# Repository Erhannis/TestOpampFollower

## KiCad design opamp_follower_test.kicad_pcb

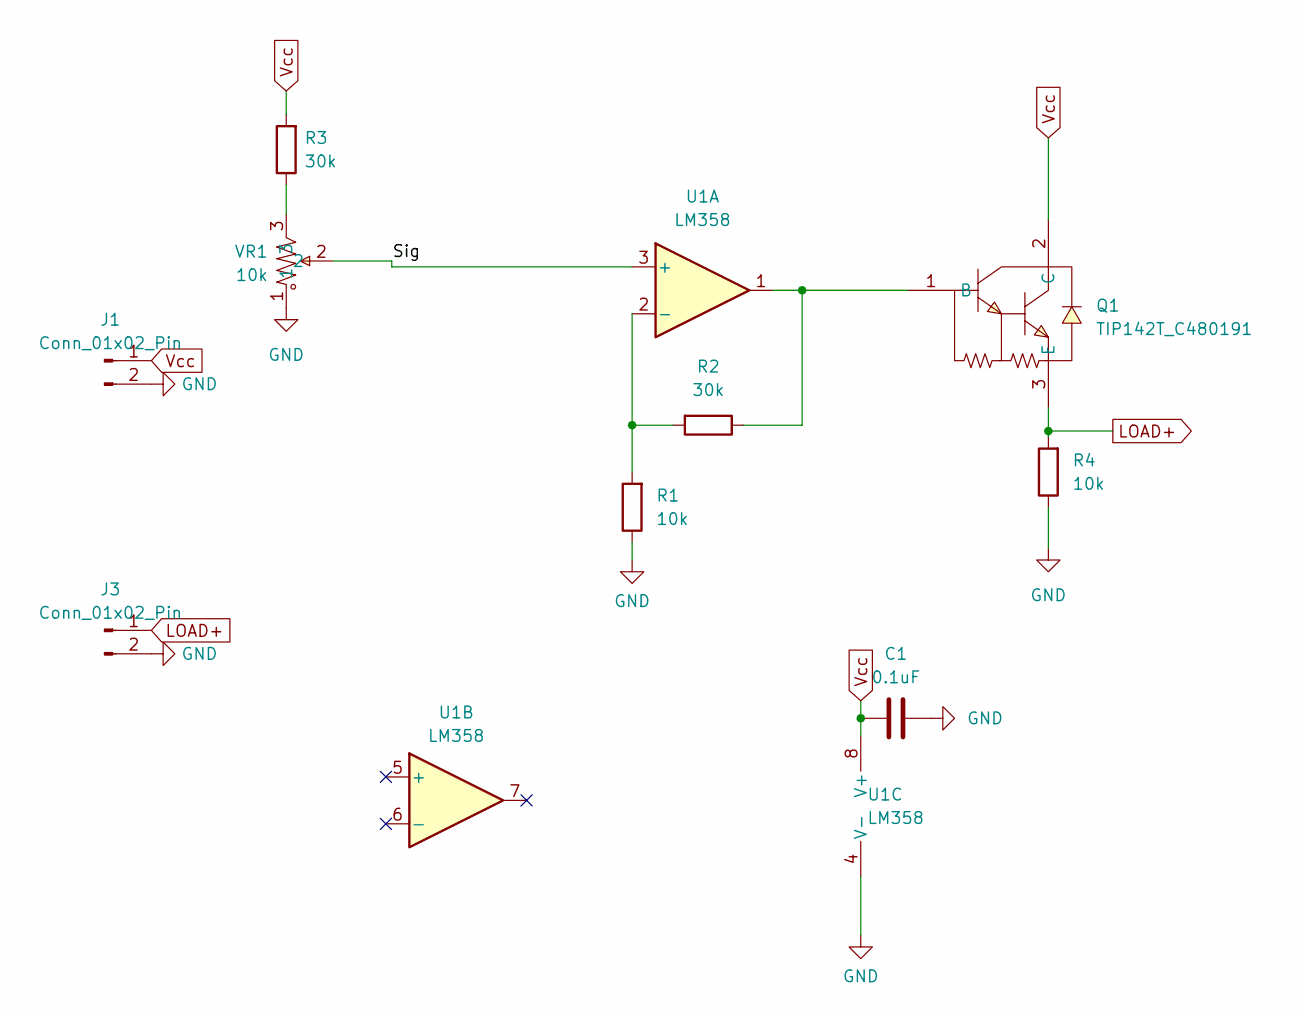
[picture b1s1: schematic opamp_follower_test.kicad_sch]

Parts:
C1: 0.1uF; C_0805_2012Metric
J1, J3: Conn_01x02_Pin; JST_NV_B02P-NV_1x02_P5.00mm_Vertical
Q1: TIP142T_C480191; TO-220-3_L10.1-W4.4-P2.54_IRF640NPBF; LCSC Part C480191
R1, R4: 10k; R_0805_2012Metric
R2, R3: 30k; R_0805_2012Metric
U1: LM358; DIP-8_W7.62mm
VR1: 10k; RES-ADJ-SMD_RM065-V1; LCSC Part C5205021

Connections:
/Sig: U1.3 (+), VR1.2
GND: C1.2, J1.2, J3.2, R1.1, R4.1, U1.4 (V-), VR1.1
LOAD+: J3.1, Q1.3 (E), R4.2
unnamed: Q1.1 (B), R2.1, U1.1
unnamed: R3.1, VR1.3
unnamed: R1.2, R2.2, U1.2 (-)
Vcc: C1.1, J1.1, Q1.2 (C), R3.2, U1.8 (V+)

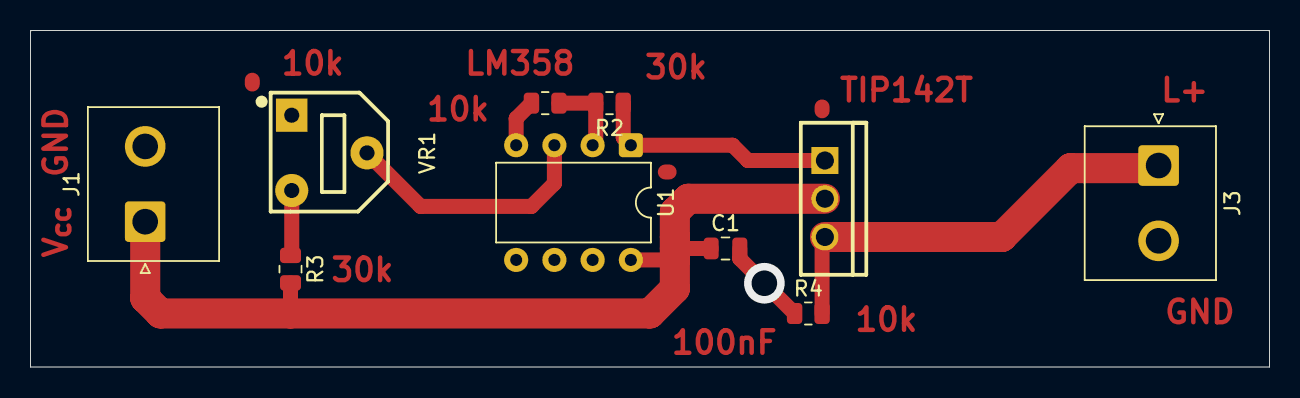
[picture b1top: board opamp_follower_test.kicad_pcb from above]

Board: 2 copper layers, 82.3 x 22.4 mm, 10 parts (0 on the bottom side), 7 nets.

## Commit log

2025-06-07 Initial draft done
2025-06-07 Added orientation marks
2025-06-07 Negacloned io
